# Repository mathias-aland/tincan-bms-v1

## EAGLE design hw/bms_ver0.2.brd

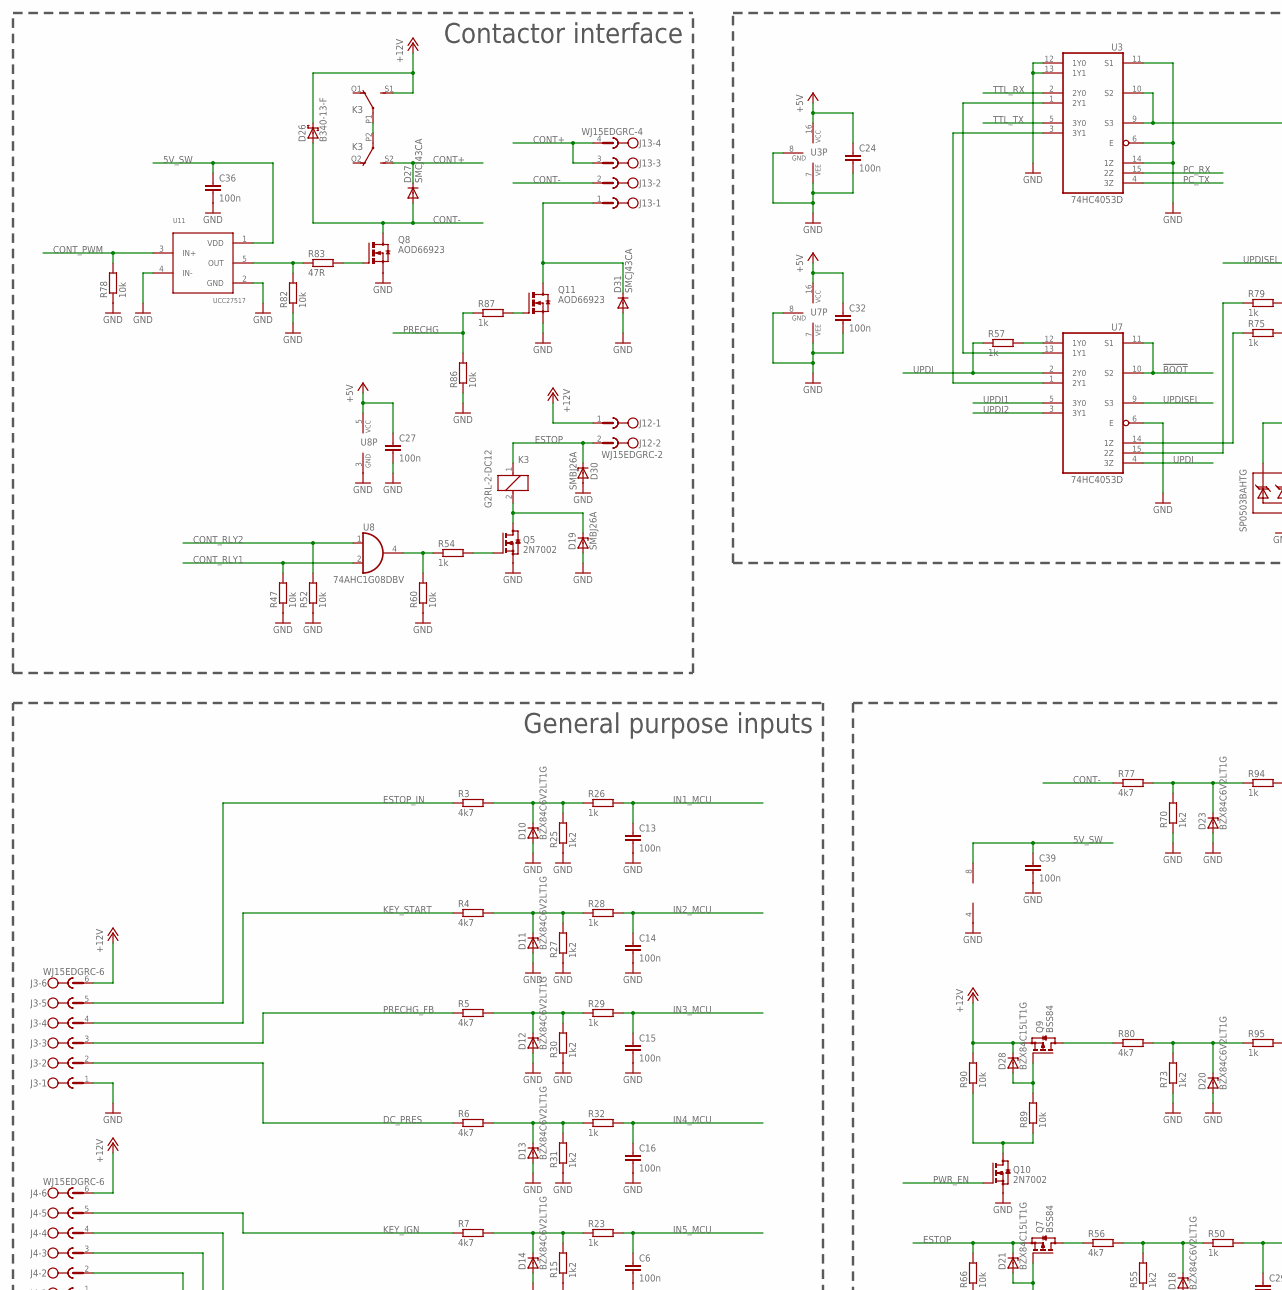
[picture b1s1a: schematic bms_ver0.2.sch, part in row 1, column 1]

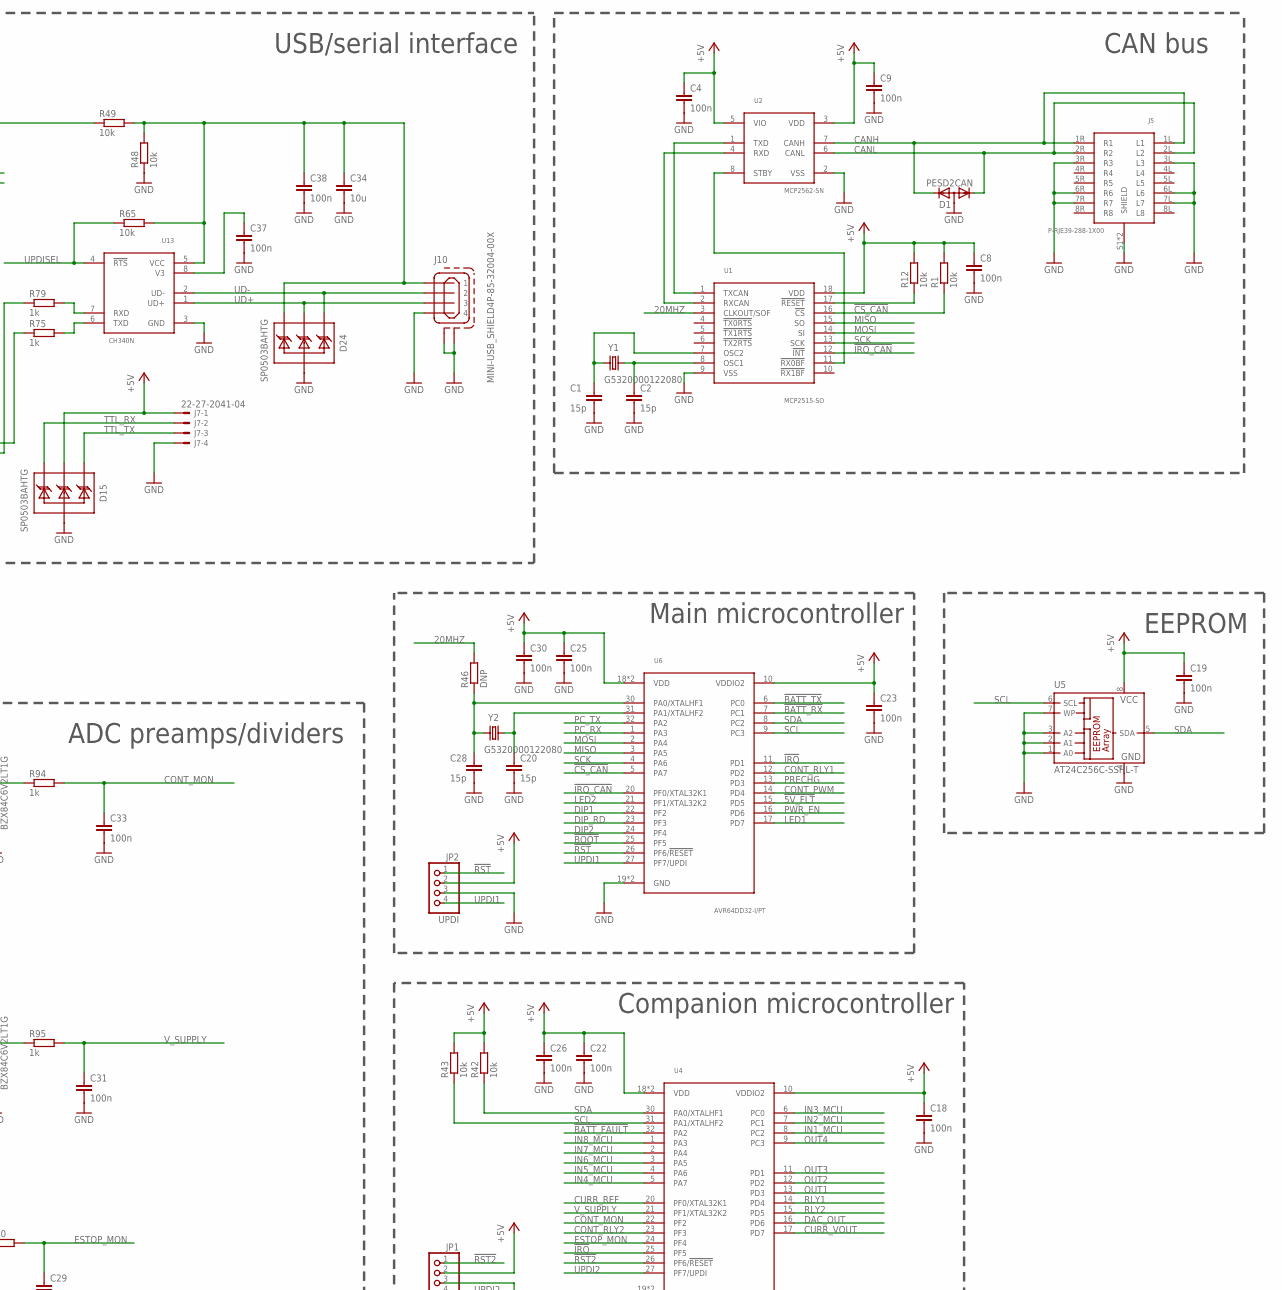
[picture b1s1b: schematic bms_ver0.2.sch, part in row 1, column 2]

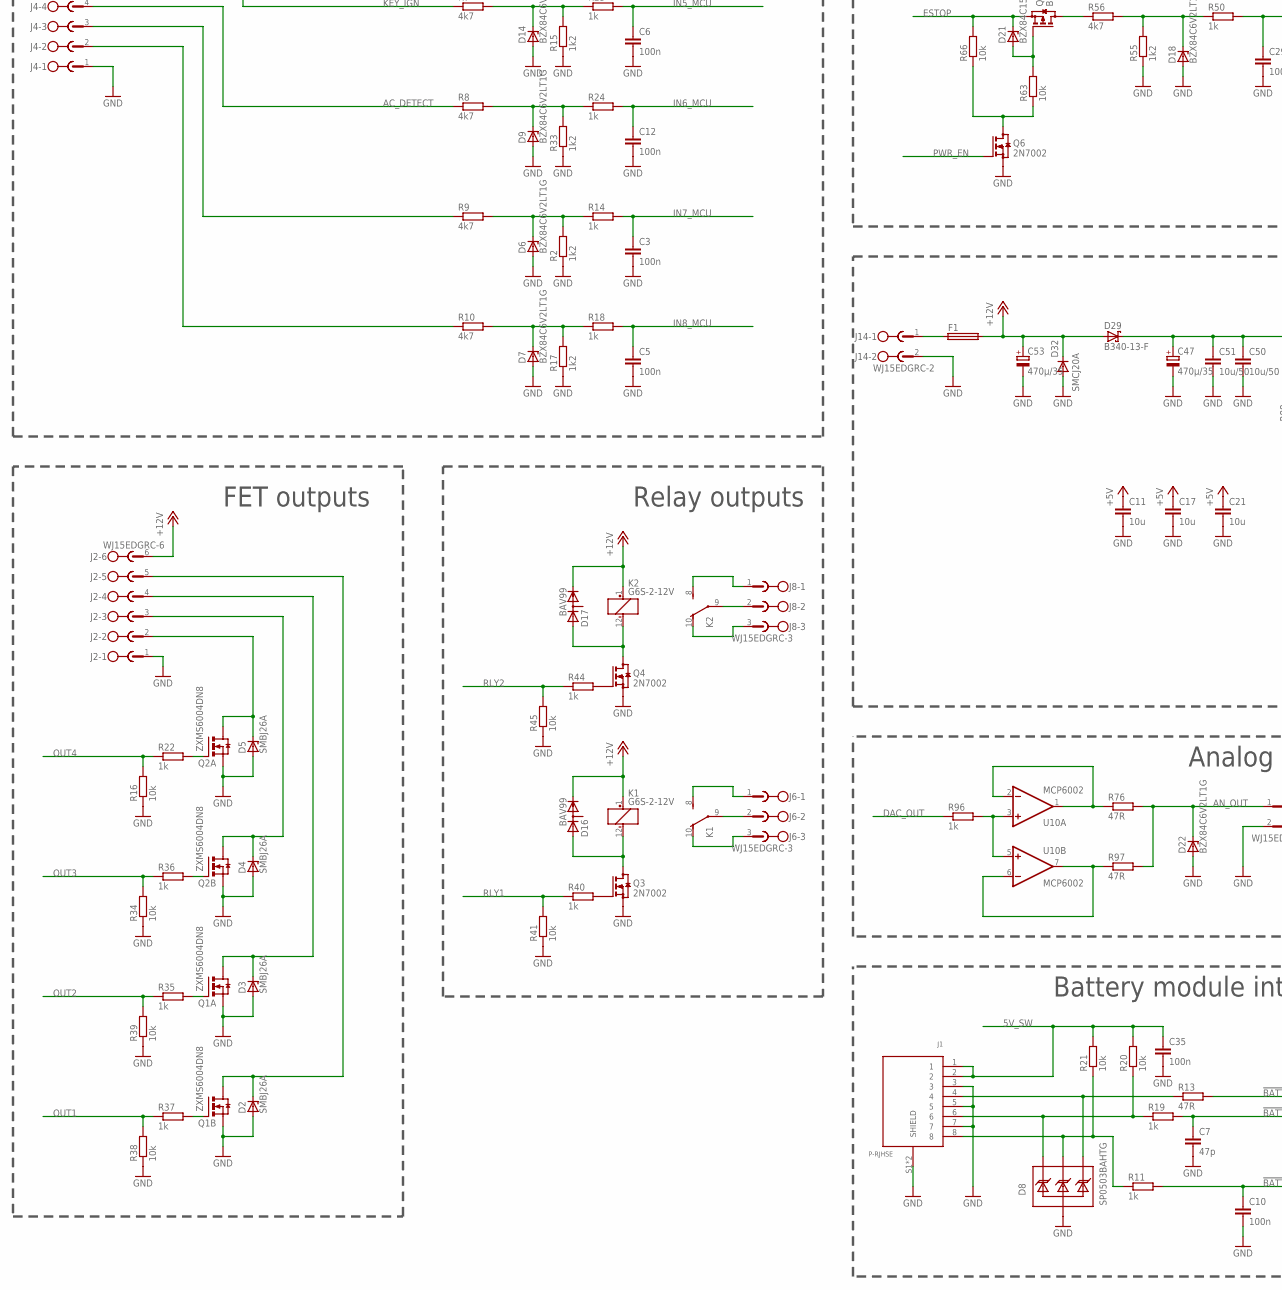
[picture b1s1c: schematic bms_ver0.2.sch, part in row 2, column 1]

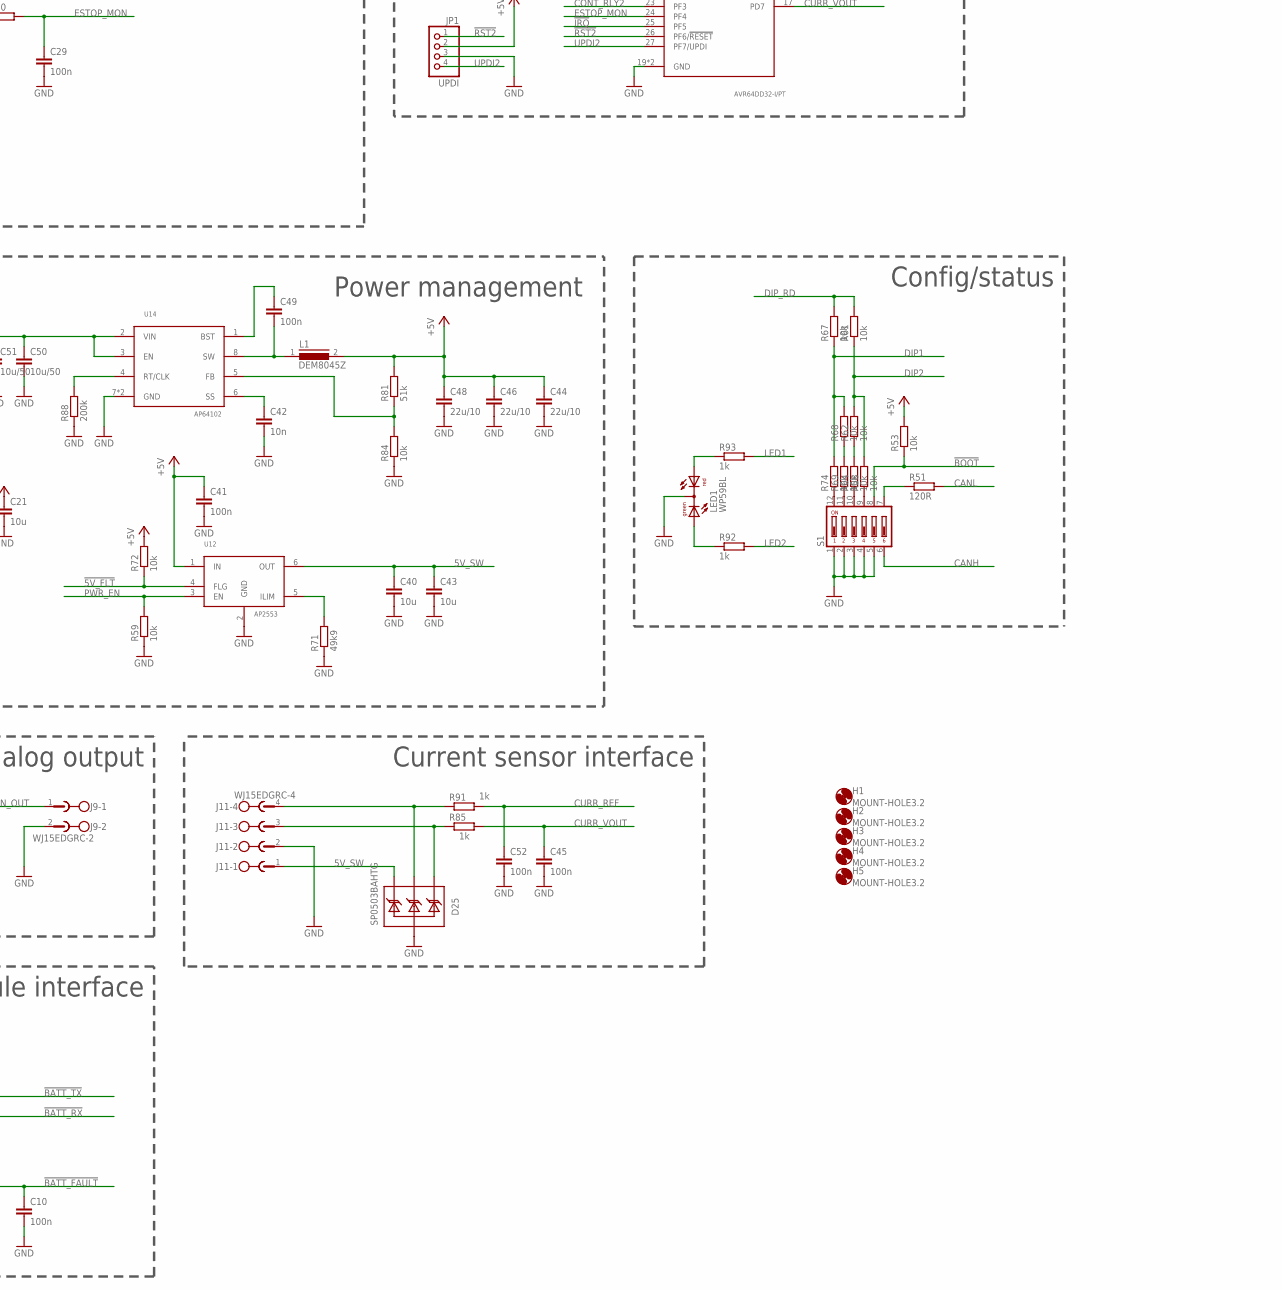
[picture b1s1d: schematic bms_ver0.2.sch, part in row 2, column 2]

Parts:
C1, C2, C20, C28: 15p; C0805K
C3, C4, C5, C6, C8, C9, C10, C12, C13, C14, C15, C16, C18, C19, C22, C23, C24, C25, C26, C27, C29, C30, C31, C32, C33, C35, C36, C37, C38, C39, C41, C45, C49, C52: 100n; C0805K
C7: 47p; C0805K
C11, C17, C21, C34, C40, C43: 10u; C1206K
C42: 10n; C0805K
C44, C46, C48: 22u/10; C1206K
C47, C53: 470µ/35; E5-10,5
C50, C51: 10u/50; C1206K
D1: PESD2CAN; SOT23
D2, D3, D4, D5, D19, D30: SMBJ26A; SMB
D6, D7, D9, D10, D11, D12, D13, D14, D18, D20, D22, D23: BZX84C6V2LT1G; SOT23
D8, D15, D24, D25: SP0503BAHTG; SOT143
D16, D17: BAV99; SOT23
D21, D28: BZX84C15LT1G; SOT23
D26, D29: B340-13-F; SMC
D27, D31: SMCJ43CA; SMC
D32: SMCJ20A; SMC
F1: 3568
H1, H2, H3, H4, H5: MOUNT-HOLE3.2; 3,2
J1: P-RJHSE
J2, J3, J4: WJ15EDGRC-6; WJ15EDGRC-3.81-6
J5: P-RJE39-288-1X00
J6, J8: WJ15EDGRC-3; WJ15EDGRC-3.81-3
J7: 22-27-2041-04; 6410-04
J9, J12, J14: WJ15EDGRC-2; WJ15EDGRC-3.81-2
J10: MINI-USB_SHIELD4P-85-32004-00X; 85-32004-00X
J11, J13: WJ15EDGRC-4; WJ15EDGRC-3.81-4
JP1, JP2: UPDI; 1X04
K1, K2: G6S-2-12V; TXD2
K3: G2RL-2-DC12; G2R2
L1: DEM8045Z
LED1: WP59BL
Q1, Q2: ZXMS6004DN8; SO-08; MOUSER 621-ZXMS6004DN8-13
Q3, Q4, Q5, Q6, Q10: 2N7002; SOT23
Q7, Q9: BSS84; SOT23
Q8, Q11: AOD66923; D-PAK_TO252AA
R1, R12, R16, R20, R21, R34, R38, R39, R41, R42, R43, R45, R47, R48, R49, R52, R53, R58, R59, R60, R61, R62, R63, R64, R65, R66, R67, R68, R69, R72, R74, R78, R82, R84, R86, R89, R90: 10k; R0805
R2, R15, R17, R25, R27, R30, R31, R33, R55, R70, R73: 1k2; R0805
R3, R4, R5, R6, R7, R8, R9, R10, R56, R77, R80: 4k7; R1206
R11, R14, R18, R19, R22, R23, R24, R26, R28, R29, R32, R35, R36, R37, R40, R44, R50, R54, R57, R75, R79, R85, R87, R91, R92, R93, R94, R95, R96: 1k; R0805
R13, R76, R83, R97: 47R; R0805
R46: DNP; R0805
R51: 120R; R1210
R71: 49k9; R0805
R81: 51k; R0805
R88: 200k; R0805
S1: DA06; DA-06
U1: MCP2515-SO; SO-18DW
U2: MCP2562-SN; SO-08
U3, U7: 74HC4053D; SO16
U4, U6: AVR64DD32-I/PT; TQFP32-08
U5: AT24C256C-SSHL-T; SO-08
U8: 74AHC1G08DBV; SOT23-5
U10: MCP6002; SO08
U11: UCC27517; SOT23-5L
U12: AP2553; SOT23-6L
U13: CH340N; SO-08
U14: AP64102; SO08-EP
Y1, Y2: G5320000122080; CRYSTAL-TXC-7A

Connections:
5V_SW: C35.1, C36.1, C39.1, C40.1, C43.1, D25.4 (C3), J1.1, J1.2, J11.1, R20.2, R21.2, U10.8 (V+), U11.1 (VDD), U12.6 (OUT)
20MHZ: R46.2, U1.3 (CLKOUT/SOF)
!5V_FLT: R72.1, U6.15 (PD5), U12.4 (FLG)
!BATT_FAULT: C10.1, R11.2, U4.32 (PA2)
!BATT_FAULT_E: D8.3 (C2), J1.8, R11.1, R21.1
!BATT_RX: C7.1, R19.2, U6.7 (PC1)
!BATT_RX_E: D8.2 (C1), J1.6, R19.1, R20.1
!BATT_TX: R13.2, U6.6 (PC0)
!BATT_TX_E: D8.4 (C3), J1.4, R13.1
!BOOT: R53.1, S1.8, U6.25 (PF5), U7.10 (S2), U7.11 (S1)
!CS_CAN: R1.1, U1.16 (!CS), U6.5 (PA7)
!IRQ: U4.25 (PF5), U6.11 (PD1)
!IRQ_CAN: U1.12 (!INT), U6.20 (PF0/XTAL32K1)
!RST: JP2.1, U6.26 (PF6/!RESET)
!RST2: JP1.1, U4.26 (PF6/!RESET)
+5V: C4.1, C8.1, C9.1, C11.1, C17.1, C18.1, C19.1, C21.1, C22.1, C23.1, C24.1, C25.1, C26.1, C27.1, C30.1, C32.1, C41.1, C44.1, C46.1, C48.1, D15.3 (C2), J7.1, JP1.2, JP2.2, L1.2, R1.2, R12.2, R42.2, R43.2, R53.2, R72.2, R81.2, U1.18 (VDD), U2.3 (VDD), U2.5 (VIO), U3.16 (VCC), U4.10 (VDDIO2), U4.18 (VDD), U4.28 (VDD), U5.8 (VCC), U6.10 (VDDIO2), U6.18 (VDD), U6.28 (VDD), U7.16 (VCC), U8.5 (VCC), U12.1 (IN)
+12V: C53.+, D16.2 (C), D17.2 (C), D26.C, D28.3 (C), D29.A, D32.C, F1.2A (2), F1.2B (2), J2.6, J3.6, J4.6, J12.1, K1.1 (+), K2.1 (+), K3.S1 (S), Q9.2 (S), R90.2
AC_DETECT: J4.4, R8.1
AC_DETECT_F: D9.3 (C), R8.2, R24.1, R33.2
AN_OUT: D22.3 (C), J9.1, R76.2, R97.2
CANH: D1.2 (K2), J5.1L (L1), J5.1R (R1), S1.6, U2.7 (CANH)
CANL: D1.1 (K1), J5.2L (L2), J5.2R (R2), R51.2, U2.6 (CANL)
CONT+: D27.C, J13.3, J13.4, K3.S2 (S)
CONT-: D26.A, D27.A, J13.2, Q8.4 (D), R77.1
CONT_MON: C33.1, R94.2, U4.22 (PF2)
CONT_PWM: R78.2, U6.14 (PD4), U11.3 (IN+)
CONT_RLY1: R47.2, U6.12 (PD2), U8.2 (I1)
CONT_RLY2: R52.2, U4.23 (PF3), U8.1 (I0)
CURR_REF: C52.1, R91.2, U4.20 (PF0/XTAL32K1)
CURR_VOUT: C45.1, R85.2, U4.17 (PD7)
DAC_OUT: R96.1, U4.16 (PD6)
DC_PRES: J3.2, R6.1
DC_PRES_F: D13.3 (C), R6.2, R31.2, R32.1
DIP1: R67.1, R68.2, R74.2, U6.22 (PF2)
DIP2: R58.2, R61.1, R62.2, U6.24 (PF4)
DIP_RD: R61.2, R67.2, U6.23 (PF3)
ESTOP: D21.3 (C), D30.C, J12.2, K3.1, Q7.2 (S), R66.2
ESTOP_IN: J3.5, R3.1
ESTOP_MON: C29.1, R50.2, U4.24 (PF4)
GND: C1.2, C2.2, C3.2, C4.2, C5.2, C6.2, C7.2, C8.2, C9.2, C10.2, C11.2, C12.2, C13.2, C14.2, C15.2, C16.2, C17.2, C18.2, C19.2, C20.2, C21.2, C22.2, C23.2, C24.2, C25.2, C26.2, C27.2, C28.2, C29.2, C30.2, C31.2, C32.2, C33.2, C34.2, C35.2, C36.2, C37.2, C38.2, C39.2, C40.2, C41.2, C42.2, C43.2, C44.2, C45.2, C46.2, C47.-, C48.2, C50.2, C51.2, C52.2, C53.-, D1.3 (A), D2.A, D3.A, D4.A, D5.A, D6.1 (A), D7.1 (A), D8.1 (A), D9.1 (A), D10.1 (A), D11.1 (A), D12.1 (A), D13.1 (A), D14.1 (A), D15.1 (A), D18.1 (A), D19.A, D20.1 (A), D22.1 (A), D23.1 (A), D24.1 (A), D25.1 (A), D30.A, D31.A, D32.A, J1.3, J1.5, J1.7, J1.S1 (SHIELD), J1.S2 (SHIELD), J2.1, J3.1, J4.1, J5.3L (L3), J5.3R (R3), J5.6L (L6), J5.6R (R6), J5.7L (L7), J5.7R (R7), J5.S1 (SHIELD), J5.S2 (SHIELD), J7.4, J9.2, J10.4, J10.M1 (S1), J10.M2 (S2), J11.2, J14.2, JP1.3, JP2.3, LED1.2 (C), Q1.1 (S), Q1.3 (S), Q2.1 (S), Q2.3 (S), Q3.2 (S), Q4.2 (S), Q5.2 (S), Q6.2 (S), Q8.3 (S), Q10.2 (S), Q11.3 (S), R2.1, R15.1, R16.1, R17.1, R25.1, R27.1, R30.1, R31.1, R33.1, R34.1, R38.1, R39.1, R41.1, R45.1, R47.1, R48.1, R52.1, R55.1, R59.1, R60.1, R70.1, R71.1, R73.1, R78.1, R82.1, R84.1, R86.1, R88.1, S1.1, S1.2, S1.3, S1.4, S1.5, U1.9 (VSS), U2.2 (VSS), U3.6 (E), U3.7 (VEE), U3.8 (GND), U3.11 (S1), U3.12 (1Y0), U3.13 (1Y1), U3.14 (1Z), U4.19 (GND), U4.29 (GND), U5.1 (A0), U5.2 (A1), U5.3 (A2), U5.4 (GND), U5.7 (WP), U6.19 (GND), U6.29 (GND), U7.6 (E), U7.7 (VEE), U7.8 (GND), U8.3 (GND), U10.4 (V-), U11.2 (GND), U11.4 (IN-), U12.2 (GND), U13.3 (GND), U14.7 (GND), U14.PAD (GND)
GPI1_F: D6.3 (C), R2.2, R9.2, R14.1
GPI2_F: D7.3 (C), R10.2, R17.2, R18.1
IN1_MCU: C13.1, R26.2, U4.8 (PC2)
IN2_MCU: C14.1, R28.2, U4.7 (PC1)
IN3_MCU: C15.1, R29.2, U4.6 (PC0)
IN4_MCU: C16.1, R32.2, U4.5 (PA7)
IN5_MCU: C6.1, R23.2, U4.4 (PA6)
IN6_MCU: C12.1, R24.2, U4.3 (PA5)
IN7_MCU: C3.1, R14.2, U4.2 (PA4)
IN8_MCU: C5.1, R18.2, U4.1 (PA3)
KEY_IGN: J4.5, R7.1
KEY_IGN_F: D14.3 (C), R7.2, R15.2, R23.1
KEY_START: J3.4, R4.1
LED1: R93.2, U6.17 (PD7)
LED2: R92.2, U6.21 (PF1/XTAL32K2)
MISO: U1.15 (SO), U6.3 (PA5)
MOSI: U1.14 (SI), U6.2 (PA4)
unnamed: R69.1, S1.11
unnamed: C1.1, U1.7 (OSC2), Y1.P$2 (2)
unnamed: C2.1, U1.8 (OSC1), Y1.P$1 (1)
unnamed: U1.1 (TXCAN), U2.1 (TXD)
unnamed: U1.2 (RXCAN), U2.4 (RXD)
unnamed: R74.1, S1.12
unnamed: R51.1, S1.7
unnamed: C37.1, U13.8 (V3)
unnamed: C28.1, R46.1, U6.30 (PA0/XTALHF1), Y2.P$2 (2)
unnamed: C20.1, U6.31 (PA1/XTALHF2), Y2.P$1 (1)
unnamed: R75.2, U13.6 (TXD)
unnamed: R75.1, U7.14 (1Z)
unnamed: R71.2, U12.5 (ILIM)
unnamed: R62.1, R64.2
unnamed: F1.1A (1), F1.1B (1), J14.1
unnamed: R82.2, R83.1, U11.5 (OUT)
unnamed: Q8.1 (G), R83.2
unnamed: R96.2, U10.3 (+IN), U10.5 (+IN)
unnamed: J6.2, K1.9
unnamed: J6.1, K1.8 (S)
unnamed: LED1.3 (AG), R92.1
unnamed: R68.1, R69.2
unnamed: LED1.1 (AR), R93.1
unnamed: R58.1, S1.9
unnamed: R64.1, S1.10
unnamed: R76.1, U10.1 (OUT), U10.2 (-IN)
unnamed: R97.1, U10.6 (-IN), U10.7 (OUT)
unnamed: C34.1, C38.1, D24.4 (C3), J10.1, R48.2, R49.2, R65.2, U13.5 (VCC)
unnamed: D11.3 (C), R4.2, R27.2, R28.1
unnamed: D31.C, J13.1, Q11.4 (D)
unnamed: D19.C, K3.2, Q5.3 (D)
unnamed: R54.1, R60.2, U8.4 (O)
unnamed: Q4.1 (G), R44.2
unnamed: Q5.1 (G), R54.2
unnamed: D17.1 (A), K2.12 (-), Q4.3 (D)
unnamed: Q3.1 (G), R40.2
unnamed: D16.1 (A), K1.12 (-), Q3.3 (D)
unnamed: J8.2, K2.9
unnamed: J8.1, K2.8 (S)
unnamed: J8.3, K2.10 (O)
unnamed: R57.2, U7.12 (1Y0)
unnamed: K3.P1, K3.P2
unnamed: Q1.2 (G), R37.2
unnamed: D25.2 (C1), J11.3, R85.1
unnamed: D25.3 (C2), J11.4, R91.1
unnamed: J4.3, R9.1
unnamed: J4.2, R10.1
unnamed: Q9.3 (D), R80.1
unnamed: J6.3, K1.10 (O)
unnamed: R79.2, U13.7 (RXD)
unnamed: Q11.1 (G), R87.2
unnamed: D12.3 (C), R5.2, R29.1, R30.2
unnamed: D18.3 (C), R50.1, R55.2, R56.2
unnamed: D28.1 (A), Q9.1 (G), R89.2
unnamed: U3.1 (2Y1), U7.13 (1Y1)
unnamed: U3.3 (3Y1), U7.1 (2Y1)
unnamed: D10.3 (C), R3.2, R25.2, R26.1
unnamed: C49.1, U14.1 (BST)
unnamed: R12.1, U1.17 (!RESET)
unnamed: D20.3 (C), R73.2, R80.2, R95.1
unnamed: C49.2, L1.1, U14.8 (SW)
unnamed: D23.3 (C), R70.2, R77.2, R94.1
unnamed: Q10.3 (D), R89.1, R90.1
unnamed: D21.1 (A), Q7.1 (G), R63.2
unnamed: R79.1, U7.15 (2Z)
unnamed: R49.1, U3.9 (S3), U3.10 (S2)
unnamed: Q6.3 (D), R63.1, R66.1
unnamed: Q7.3 (D), R56.1
unnamed: R81.1, R84.2, U14.5 (FB)
unnamed: C42.1, U14.6 (SS)
unnamed: U1.11 (!RX0BF), U2.8 (STBY)
unnamed: R88.2, U14.4 (RT/CLK)
unnamed: C47.+, C50.1, C51.1, D29.C, U14.2 (VIN), U14.3 (EN)
unnamed: D5.C, J2.2, Q2.5 (D), Q2.6 (D)
unnamed: D2.C, J2.5, Q1.7 (D), Q1.8 (D)
unnamed: D3.C, J2.4, Q1.5 (D), Q1.6 (D)
unnamed: D4.C, J2.3, Q2.7 (D), Q2.8 (D)
unnamed: Q2.4 (G), R22.2
unnamed: Q2.2 (G), R36.2
unnamed: Q1.4 (G), R35.2
OUT1: R37.1, R38.2, U4.13 (PD3)
OUT2: R35.1, R39.2, U4.12 (PD2)
OUT3: R34.2, R36.1, U4.11 (PD1)
OUT4: R16.2, R22.1, U4.9 (PC3)
PC_RX: U3.15 (2Z), U6.1 (PA3)
PC_TX: U3.4 (3Z), U6.32 (PA2)
PRECHG: R86.2, R87.1, U6.13 (PD3)
PRECHG_FB: J3.3, R5.1
PWR_EN: Q6.1 (G), Q10.1 (G), R59.2, U6.16 (PD6), U12.3 (EN)
RLY1: R40.1, R41.2, U4.14 (PD4)
RLY2: R44.1, R45.2, U4.15 (PD5)
SCK: U1.13 (SCK), U6.4 (PA6)
SCL: R43.1, U4.31 (PA1/XTALHF2), U5.6 (SCL), U6.9 (PC3)
SDA: R42.1, U4.30 (PA0/XTALHF1), U5.5 (SDA), U6.8 (PC2)
TTL_RX: D15.4 (C3), J7.2, U3.2 (2Y0)
TTL_TX: D15.2 (C1), J7.3, U3.5 (3Y0)
UD+: D24.3 (C2), J10.3, U13.1 (UD+)
UD-: D24.2 (C1), J10.2, U13.2 (UD-)
UPDI: R57.1, U7.2 (2Y0), U7.4 (3Z)
UPDI1: JP2.4, U6.27 (PF7/UPDI), U7.5 (3Y0)
UPDI2: JP1.4, U4.27 (PF7/UPDI), U7.3 (3Y1)
UPDISEL: R65.1, U7.9 (S3), U13.4 (!RTS)
V_SUPPLY: C31.1, R95.2, U4.21 (PF1/XTAL32K2)

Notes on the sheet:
FET outputs
Relay outputs
Power management
USB/serial interface
CAN bus
EEPROM
Main microcontroller
Config/status
Battery module interface
General purpose inputs
Companion microcontroller
Contactor interface
Analog output
ADC preamps/dividers
Current sensor interface

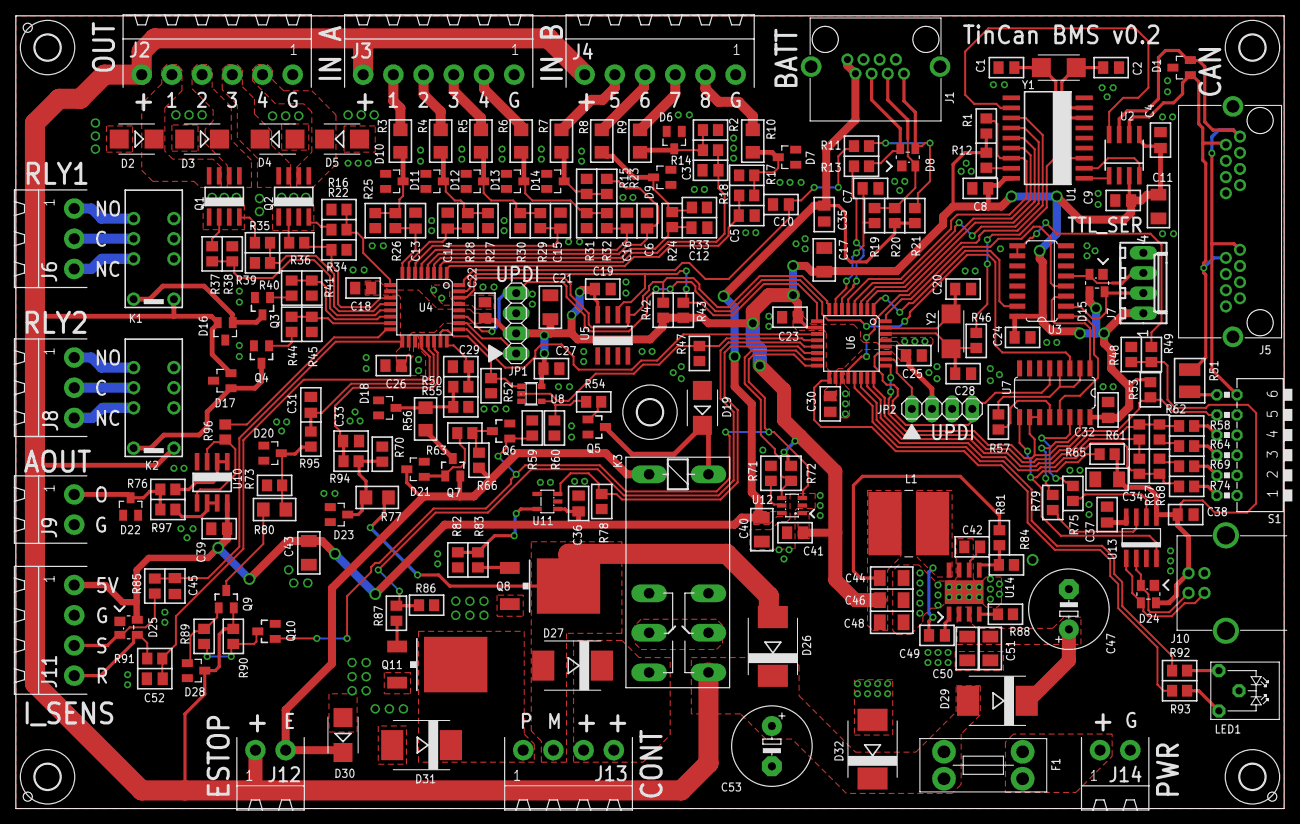
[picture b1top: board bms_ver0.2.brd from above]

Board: 2 copper layers, 160.0 x 100.0 mm, 236 parts (0 on the bottom side), 160 nets.

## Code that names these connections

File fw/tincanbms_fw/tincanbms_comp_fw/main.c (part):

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	.sys_alarms = 0x01,
	.dac_val = 0x03ff,
	.mcu_temp = 0,
	.v_supply = 0,
	.vdd = 0,
	.i_sense = 0,
	.cont_mon = 0,
	.i_ref = 0,
	.i_diag = 0,
	.estop_mon = 0,
	.inp_state = 0,
	.inp_v = {[0 ... 7] = 0},
	.inp_lo_threshold = {[0 ... 7] = 0xff},
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					if (outState_tmp & 0x01)
					{
						// OUT1 = ON
						PORTD.OUTSET = PIN3_bm;	// PD3 = 1
					}
					else
					{
						// OUT1 = OFF
						PORTD.OUTCLR = PIN3_bm;	// PD3 = 0
					}
					
					uint8_t ctrlb_tmp = TCA_SINGLE_WGMODE_SINGLESLOPE_gc;
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					switch (outState_tmp & 0x06)
					{
						case (OUT_STATE_OFF << 1):
							// OUT2 GPIO mode, off
							PORTD.OUTCLR = PIN2_bm;						// PD2 = 0
							break;
						case (OUT_STATE_ON << 1):
							// OUT2 GPIO mode, on
							PORTD.OUTSET = PIN2_bm;						// PD2 = 1
							break;
						case (OUT_STATE_PWM << 1):
							// OUT2 PWM mode
							PORTD.PIN2CTRL &= ~PORT_INVEN_bm;			// PD2 not inverted
							ctrlb_tmp |= TCA_SINGLE_CMP2EN_bm;			// enable PWM output
							break;
						case (OUT_STATE_PWM_INV << 1):
							// OUT2 inverted PWM mode
							PORTD.PIN2CTRL |= PORT_INVEN_bm;			// PD2 inverted
							ctrlb_tmp |= TCA_SINGLE_CMP2EN_bm;			// enable PWM output
							break;
					}
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					switch (outState_tmp & 0x18)
					{
						case (OUT_STATE_OFF << 3):
							// OUT3 GPIO mode, off
							PORTD.OUTCLR = PIN1_bm;						// PD1 = 0
							break;
						case (OUT_STATE_ON << 3):
							// OUT3 GPIO mode, on
							PORTD.OUTSET = PIN1_bm;						// PD1 = 1
							break;
						case (OUT_STATE_PWM << 3):
							// OUT3 PWM mode
							PORTD.PIN1CTRL &= ~PORT_INVEN_bm;			// PD1 not inverted
							ctrlb_tmp |= TCA_SINGLE_CMP1EN_bm;			// enable PWM output
							break;
						case (OUT_STATE_PWM_INV << 3):
							// OUT3 inverted PWM mode
							PORTD.PIN1CTRL |= PORT_INVEN_bm;			// PD1 inverted
							ctrlb_tmp |= TCA_SINGLE_CMP1EN_bm;			// enable PWM output
							break;
					}
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					if (outState_tmp & 0x20)
					{
						// OUT4 = ON
						PORTC.OUTSET = 0x08;	// PC3 = 1
					}
					else
					{
						// OUT4 = OFF
						PORTC.OUTCLR = 0x08;	// PC3 = 0
					}
					
					if (outState_tmp & 0x40)
					{
						// RLY1 = ON
						PORTD.OUTSET = 0x10;	// PD4 = 1
					}
					else
					{
						// RLY1 = OFF
						PORTD.OUTCLR = 0x10;	// PD4 = 0
					}
					
					if (outState_tmp & 0x80)
					{
						// RLY2 = ON
						PORTD.OUTSET = 0x20;	// PD5 = 1
					}
					else
					{
						// RLY2 = OFF
						PORTD.OUTCLR = 0x20;	// PD5 = 0
					}		
					
					
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								//EVSYS.SWEVENTA = EVSYS_SWEVENTA_CH3_gc;
								params.cont_state = CONT_STATE_FAULT_ESTOP;
							}
							else if (PORTA.IN & PIN2_bm)	// check PA2 (FAULT)
							{
								// pin high = no fault
								// enable contactor
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		PORTF.OUTCLR = PIN3_bm;
			
		TCA0.SINGLE.CTRLB = TCA_SINGLE_WGMODE_SINGLESLOPE_gc;
		PORTD.OUTCLR = PIN3_bm | PIN2_bm | PIN1_bm | PIN4_bm | PIN5_bm;		// PD3 = 0, PD2 = 0, PD1 = 0, PD4 = 0, PD5 = 0
		PORTC.OUTCLR = PIN3_bm;		// PC3 = 0
		DAC0.DATA = 0;
			
			
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	PORTD.PORTCTRL = PORT_SRL_bm;   // Port D slew rate limit on
	PORTF.PORTCTRL = PORT_SRL_bm;   // Port F slew rate limit on
	
	//PORTF.PIN0CTRL |= PORT_PULLUPEN_bm;	// PF0 pullup enable
	//PORTD.PIN7CTRL |= PORT_PULLUPEN_bm;	// PD7 pullup enable
	
	PORTA.PIN0CTRL |= PORT_PULLUPEN_bm;	// PA0 pullup enable (SDA)
	PORTA.PIN1CTRL |= PORT_PULLUPEN_bm;	// PA1 pullup enable (SCL)
	
	/* PORTMUX Initialization */
	PORTMUX.TWIROUTEA = PORTMUX_TWI0_ALT3_gc;       // TWI0 on PA0/1
	PORTMUX.TCAROUTEA = PORTMUX_TCA0_PORTD_gc;		// TCA0 on port D
	
	/* Clock init */
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	ADC0.INTFLAGS = ADC_RESRDY_bm | ADC_WCMP_bm;	// clear interrupt flags
	ADC0.INTCTRL = ADC_RESRDY_bm;					// enable interrupt
	
	//// configure FAULT input (PA2) to trigger TCA0 via EVSYS CH0
	//EVSYS.CHANNEL0 = EVSYS_CHANNEL0_PORTA_PIN2_gc;
	//EVSYS.USERTCA0CNTB = EVSYS_USER_CHANNEL0_gc;
	//
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
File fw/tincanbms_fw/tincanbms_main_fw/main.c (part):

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    PORTF.PORTCTRL = PORT_SRL_bm;   // Port F slew rate limit on

  /* PORTMUX Initialization */
    PORTMUX.SPIROUTEA = PORTMUX_SPI0_DEFAULT_gc;    // SPI0 on PA4/5/6/7
    PORTMUX.TCDROUTEA = PORTMUX_TCD0_ALT4_gc;       // TCD0 on PA4/PA5/PD4/PD5
    PORTMUX.TWIROUTEA = PORTMUX_TWI0_ALT2_gc;       // TWI0 on PC2/3
    PORTMUX.USARTROUTEA = PORTMUX_USART0_ALT2_gc | PORTMUX_USART1_DEFAULT_gc;   // USART0 on PA2/3, USART1 on PC0/1
	
	
	
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
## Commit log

2024-04-16 Add code
2024-04-16 Add PCB schematic/layout
2024-04-17 Misc fixes in FW/SW
    - Add more debug stats
    - Improve comm fault flag handling for battery modules
    - Change default fault/alert mask bits
    - Improve pump/heater logic
    - Double buffering and increased number of decimals in config utility
2024-04-21 Fix cell balancing logic
2024-04-25 Rewrite balancing logic
    Also add ability to enter BOOT mode from software, HW mod needed: wire jumper from U1 (MCP2515) pin 10 to S1 (DIP switch) position 5 (signal side, not ground side)
2024-12-16 Various bug fixes and improvements

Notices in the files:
parts and their libraries:
SparkFun-FreqCtrl: Licensing: Creative Commons ShareAlike 4.0 International - https://creativecommons.org/licenses/by-sa/4.0
